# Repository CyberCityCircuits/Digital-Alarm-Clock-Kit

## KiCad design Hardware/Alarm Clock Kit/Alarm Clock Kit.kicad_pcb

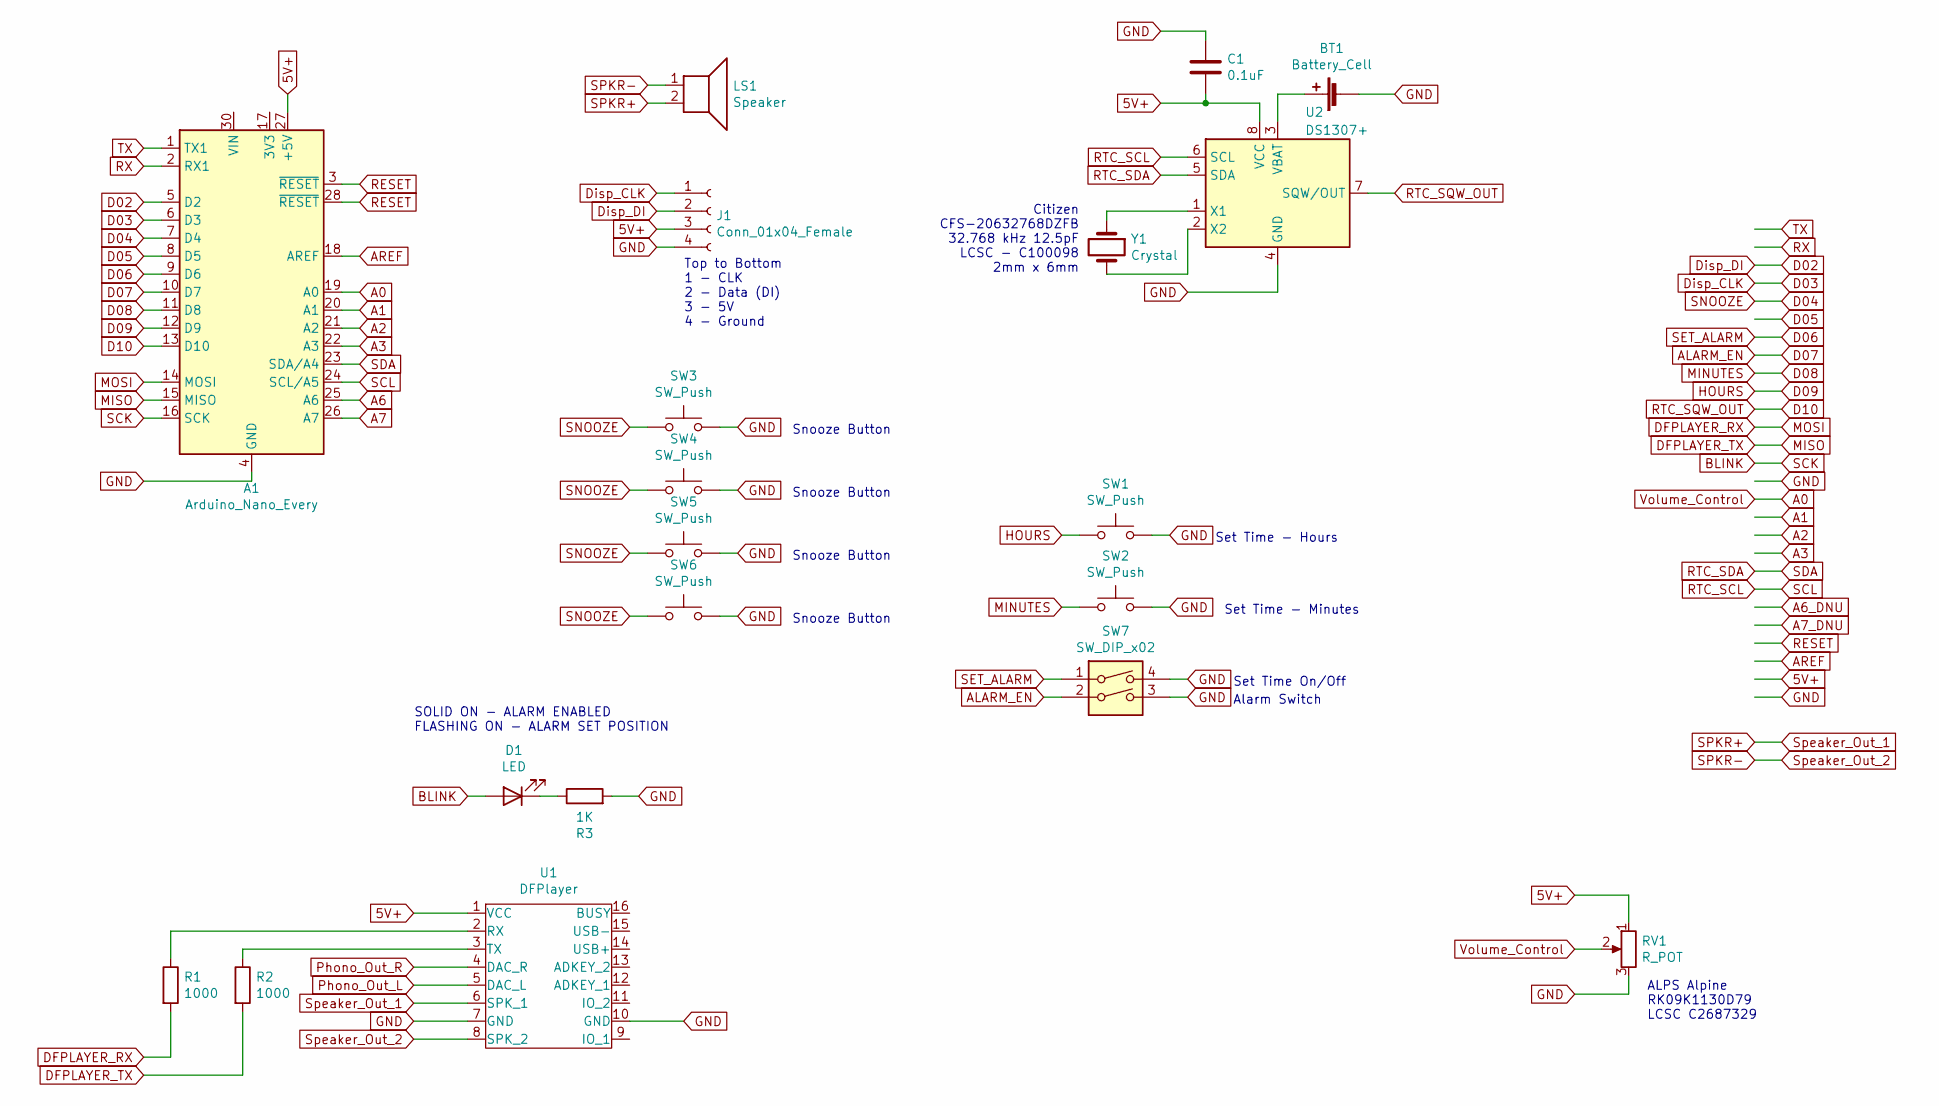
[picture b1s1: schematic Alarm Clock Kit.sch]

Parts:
A1: Arduino_Nano_Every; Arduino_Nano
BT1: Battery_Cell; Schematic - Battery CR2032
C1: 0.1uF; Schematic - Capacitor 5.0mm
D1: LED; Schematic - LED 5mm(2.56P) 003
J1: Conn_01x04_Female; TM1637-4-Digit-Display
LS1: Speaker; Speaker_Large_Fuet
R1, R2: 1000; Schematic - Resistor 10.00mm
R3: 1K; Schematic - Resistor 10.00mm
RV1: R_POT; Potentiometer_Alps_RK09L_Single_Vertical
SW1, SW2, SW3, SW4, SW5, SW6: SW_Push; Schematic - Push Button 6.5x4.5
SW7: SW_DIP_x02; SW_DIP_SPSTx02_Slide_6.7x6.64mm_W7.62mm_P2.54mm_LowProfile
U1: DFPlayer; DFPlayer_V2
U2: DS1307+; DIP-8_W7.62mm
Y1: Crystal; Crystal_C26-LF_D2.1mm_L6.5mm_Horizontal

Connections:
5V+: A1.27 (+5V), C1.2, J1.3, RV1.1, U1.1 (VCC), U2.8 (VCC)
A0: A1.19 (A0), RV1.2
A1: A1.20 (A1)
A2: A1.21 (A2)
A3: A1.22 (A3)
A6: A1.25 (A6)
A7: A1.26 (A7)
ALARM_EN: A1.10 (D7), SW7.2
AREF: A1.18 (AREF)
BLINK: A1.16 (SCK), D1.2 (A)
D02: A1.5 (D2), J1.2
D03: A1.6 (D3), J1.1
D04: A1.7 (D4), SW3.1, SW4.1, SW5.1, SW6.1
D05: A1.8 (D5)
D06: A1.9 (D6), SW7.1
D08: A1.11 (D8), SW2.1
D09: A1.12 (D9), SW1.1
D10: A1.13 (D10), U2.7 (SQW/OUT)
DFPLAYER_RX: A1.14 (MOSI), R1.2
DFPLAYER_TX: A1.15 (MISO), R2.2
GND: A1.4 (GND), A1.29 (GND), BT1.2 (-), C1.1, J1.4, R3.2, RV1.3, SW1.2, SW2.2, SW3.2, SW4.2, SW5.2, SW6.2, SW7.3, SW7.4, U1.7 (GND), U1.10 (GND), U2.4 (GND)
unnamed: BT1.1 (+), U2.3 (VBAT)
unnamed: D1.1 (K), R3.1
unnamed: R1.1, U1.2 (RX)
unnamed: R2.1, U1.3 (TX)
unnamed: U2.1 (X1), Y1.1
unnamed: U2.2 (X2), Y1.2
Phono_Out_L: U1.5 (DAC_L)
Phono_Out_R: U1.4 (DAC_R)
RESET: A1.3 (~RESET), A1.28 (~RESET)
RTC_SCL: A1.24 (SCL/A5), U2.6 (SCL)
RTC_SDA: A1.23 (SDA/A4), U2.5 (SDA)
RX: A1.2 (RX1)
SPKR+: LS1.2, U1.6 (SPK_1)
SPKR-: LS1.1, U1.8 (SPK_2)
TX: A1.1 (TX1)

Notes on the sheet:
Top to Bottom 1 - CLK 2 - Data (DI) 3 - 5V 4 - Ground
Set Time On/Off
Set Time - Hours
Set Time - Minutes
ALPS Alpine RK09K1130D79 LCSC C2687329
SOLID ON - ALARM ENABLED FLASHING ON - ALARM SET POSITION
Citizen CFS-20632768DZFB 32.768 kHz 12.5pF LCSC - C100098 2mm x 6mm
Alarm Switch
Snooze Button

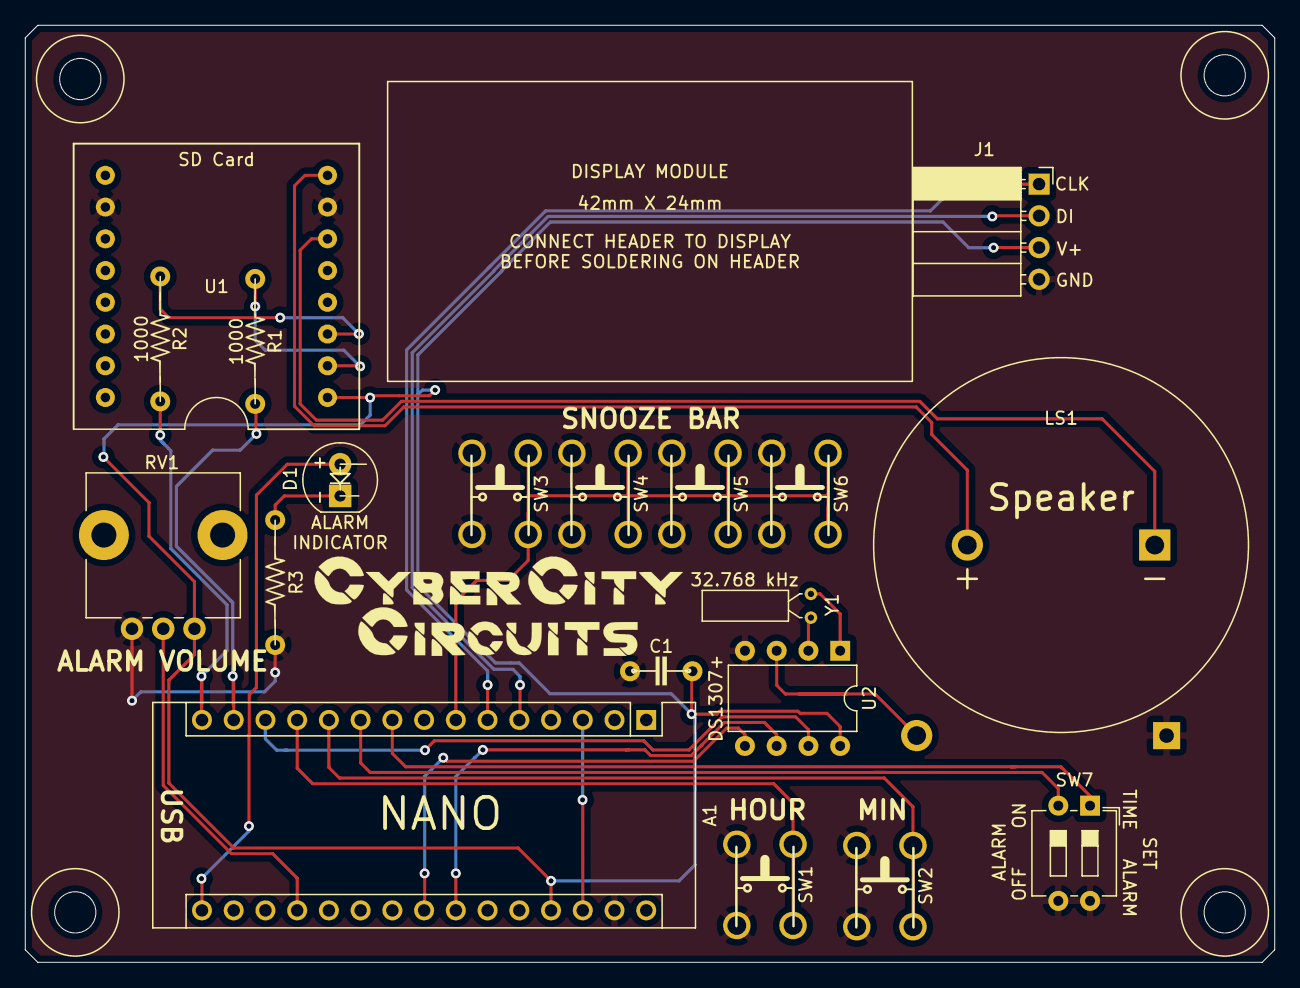
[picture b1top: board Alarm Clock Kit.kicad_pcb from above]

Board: 2 copper layers, 100.0 x 75.0 mm, 24 parts (1 on the bottom side), 25 nets.

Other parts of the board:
 : 3mm_Hole; 3mm Mount Hole
 #2,  #3,  #4: 3mm_Hole; 3mm Mount Hole

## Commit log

2021-08-03 Init
2021-08-03 Updated Software
